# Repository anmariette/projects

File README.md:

# Air Pollution Monitoring with SMS Reporting – KiCad Design

## Overview
This repository contains the **KiCad schematic and PCB design files** for an Air Pollution Monitoring system with SMS reporting. The system is designed to track harmful gases and air quality levels in industrial and urban environments using multiple gas sensors. When pollution exceeds a set threshold, the system triggers alerts through a buzzer and sends **real-time SMS notifications** via the SIM900 GSM module, enabling proactive safety measures.

## Repository Contents
- `/schematics` → KiCad schematic files (.sch)  
- `/pcb` → PCB layout design (.kicad_pcb)  
- `/gerber` → Generated Gerber files for PCB manufacturing  
- `/3d` → 3D board visualization   

## Components in the Design
- **Arduino Uno interface** (MCU connections)  
- **MQ135 Gas Sensors (x2)** – Detect CO₂, NH₃, Benzene, etc.  
- **MQ9 Sensor** – Detects CO and combustible gases  
- **DHT Sensor** – Monitors temperature and humidity  
- **SIM900 GSM Module** – Sends SMS alerts  
- **Buzzer** – Local alert for high pollution levels

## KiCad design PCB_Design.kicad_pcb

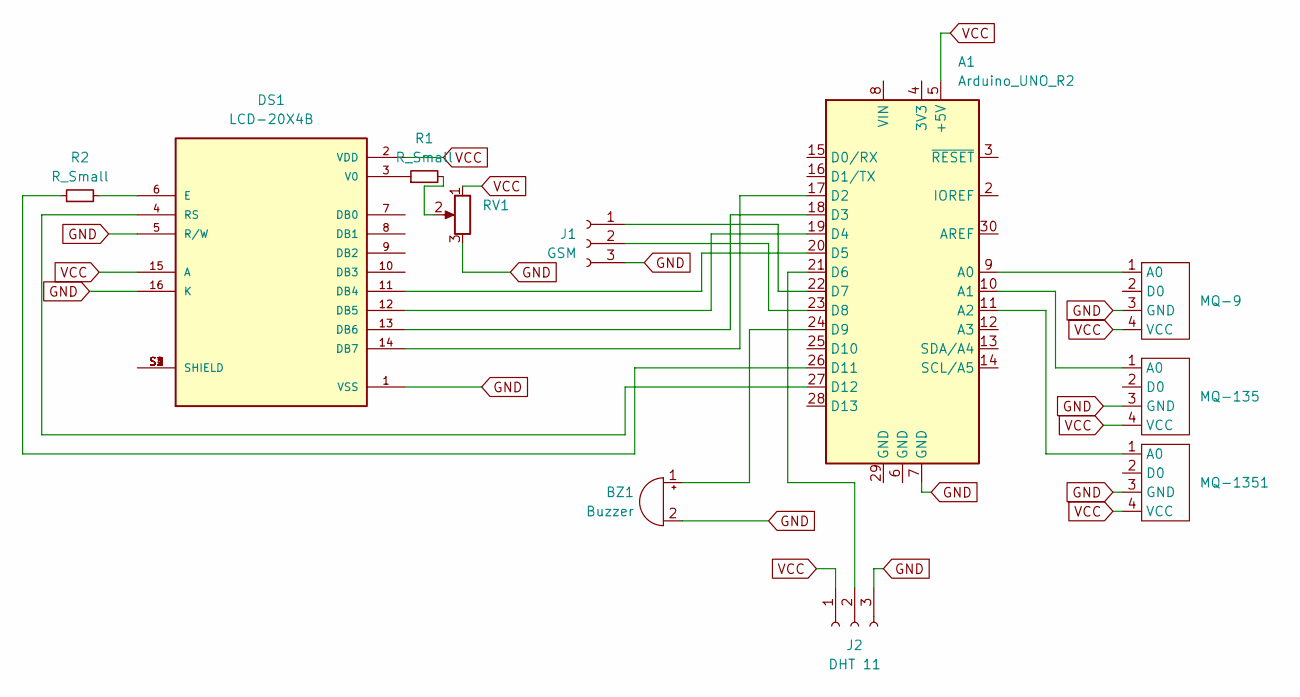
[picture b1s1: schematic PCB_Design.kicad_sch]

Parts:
A1: Arduino_UNO_R2
BZ1: Buzzer; Buzzer_12x9.5RM7.6
DS1: LCD-20X4B; LCD_LCD-20X4B; PARTREV N/A
J1: GSM; PinSocket_1x03_P2.54mm_Vertical
J2: DHT 11; PinSocket_1x03_P2.54mm_Vertical
MQ-9, MQ-135, MQ-1351: MQ-9
R1: R_Small; R_Axial_DIN0207_L6.3mm_D2.5mm_P7.62mm_Horizontal
R2: R_Small; R_Axial_DIN0204_L3.6mm_D1.6mm_P5.08mm_Horizontal
RV1: R_Potentiometer; Potentiometer_Piher_T-16H_Single_Horizontal

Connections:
GND: A1.7 (GND), BZ1.2 (-), DS1.1 (VSS), DS1.5 (R/W), DS1.16 (K), J1.3, J2.3, MQ-9.3 (GND), MQ-135.3 (GND), MQ-1351.3 (GND), RV1.3
unnamed: A1.9 (A0), MQ-9.1 (A0)
unnamed: A1.10 (A1), MQ-135.1 (A0)
unnamed: A1.11 (A2), MQ-1351.1 (A0)
unnamed: A1.17 (D2), DS1.14 (DB7)
unnamed: A1.18 (D3), DS1.13 (DB6)
unnamed: A1.19 (D4), DS1.12 (DB5)
unnamed: A1.20 (D5), DS1.11 (DB4)
unnamed: A1.21 (D6), J2.2
unnamed: A1.22 (D7), J1.1
unnamed: A1.23 (D8), J1.2
unnamed: A1.24 (D9), BZ1.1 (+)
unnamed: A1.26 (D11), R2.1
unnamed: A1.27 (D12), DS1.4 (RS)
unnamed: DS1.6 (E), R2.2
unnamed: DS1.S1 (SHIELD), DS1.S2 (SHIELD), DS1.S3 (SHIELD), DS1.S4 (SHIELD)
unnamed: DS1.3 (V0), R1.1
unnamed: R1.2, RV1.2
VCC: A1.5 (+5V), DS1.2 (VDD), DS1.15 (A), J2.1, MQ-9.4 (VCC), MQ-135.4 (VCC), MQ-1351.4 (VCC), RV1.1

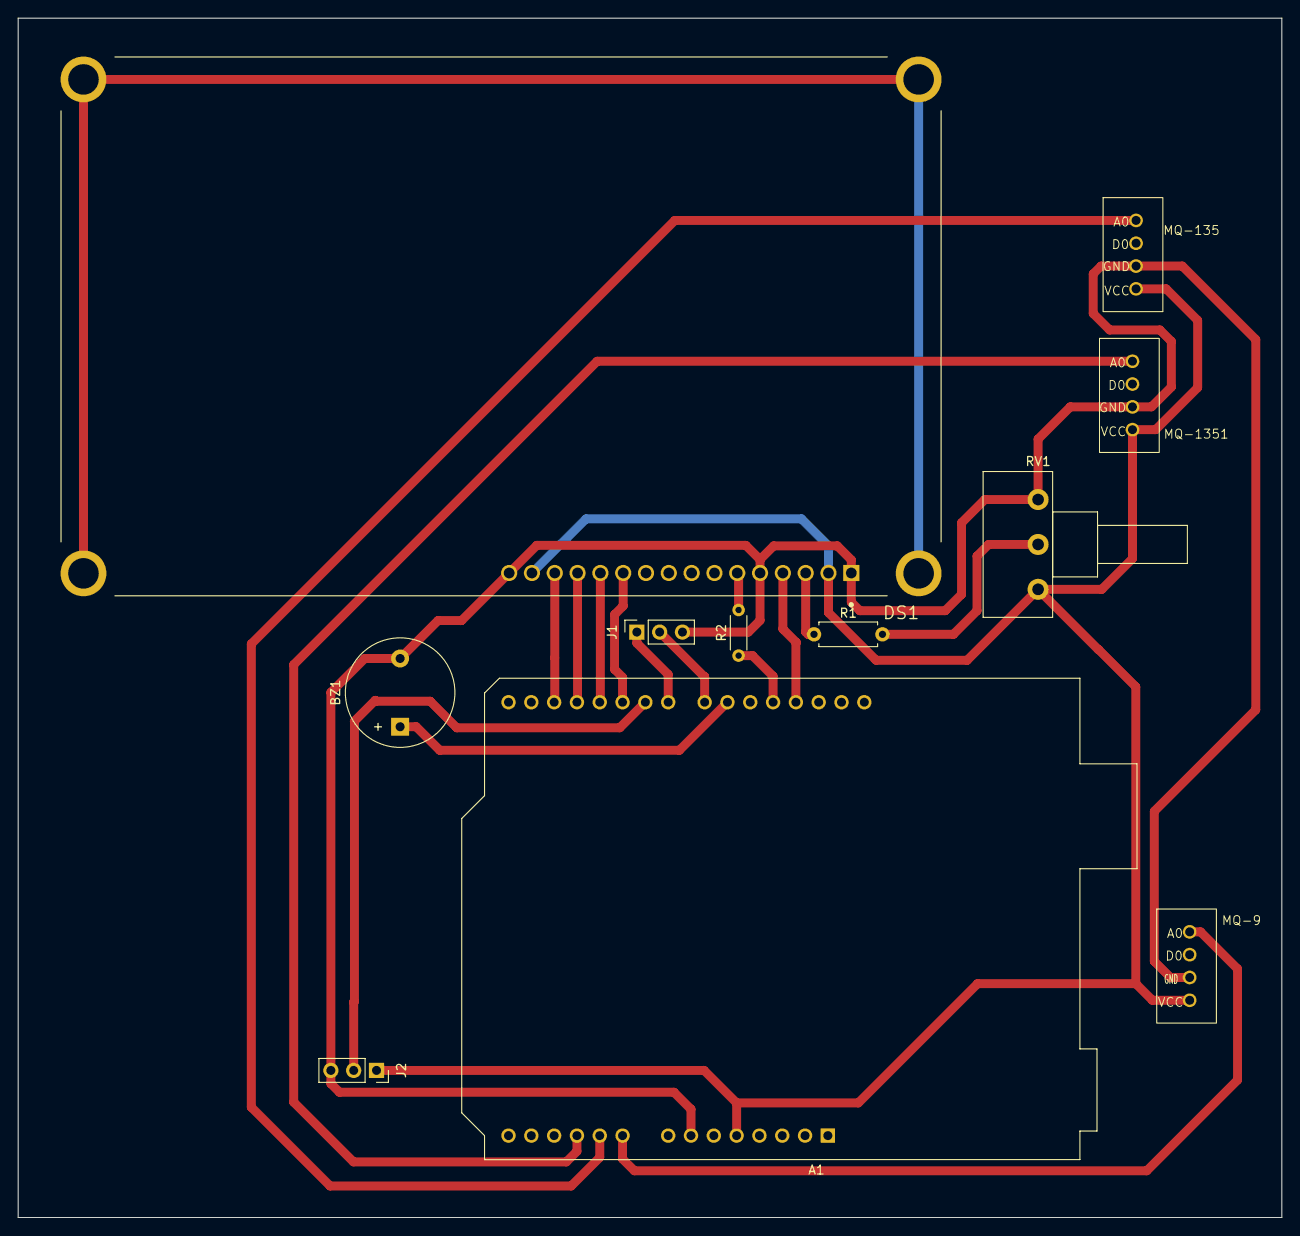
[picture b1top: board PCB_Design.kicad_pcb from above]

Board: 2 copper layers, 140.7 x 133.5 mm, 11 parts (0 on the bottom side), 19 nets.
